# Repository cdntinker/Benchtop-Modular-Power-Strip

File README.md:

Yay...

GitHub borked...

Good thing I'm in the abit of backing things up locally too.

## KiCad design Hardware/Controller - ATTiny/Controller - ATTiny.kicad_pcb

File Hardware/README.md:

# The hardware (duh...)

Each folder here is a standalone KiCAD project for a part of this overall system.

(Tho **KiCAD Customs** is a special case, it contains custom libraries used in this project & **Retired Parts** is aptly named....)

## Backplane
This is the "daisy-chainable" backplane for the modules to plug into.

## Module - *
To create a new module... Just copy one of the **WIP - Prototyping Module** folders, do some renaming & go from there.
* Module - TPS540x
  - a fixed voltage output module based on the TPS540x family of chips.
  - Can be populated with either the 3v3 or 5v0 version (possibly others if they exist)
  - Basic design has dual circuits
  - Options for USB-A/C or XT30 combo footprint
* Module - LM2596S
  - a fixed voltage output module based on the LM2596S
  - Output voltage(s) set via resistors R502/R503 & R602/603
  - Basic design has dual circuits
  - Options for USB-A/C or XT30 combo footprint
* Module - USB QC
  - A QC 2.0 output module
* Module - USB PD Source
  - Take a guess...
  - (I _think_ I've got this one worked out...)

## Master Control Modules
* Controller - ATTiny
  - So far, this is the default.
  - (Seeing as it's basically the same controller as all the modules with USB added...)
* Controller - ESP32
  - WIP
* Controller - ESP8266
  - WIP
* Controller - RP2040
  - WIP

## Testing & Prototyping Modules
* WIP - Prototyping Module
  - Another option as a new module starting point...
* WIP - **Sumpin Random**
  - Could be anything I'm still working through...
* Module - ATTiny Breakout
  - Sort of a module for messing about with the ATTiny...
* Tool - ATTiny Module Flasher
  - A UPDI Module flashing tool
* Tool - ESP Module Flasher
  - An offshoot of the ATTiny Module Flasher

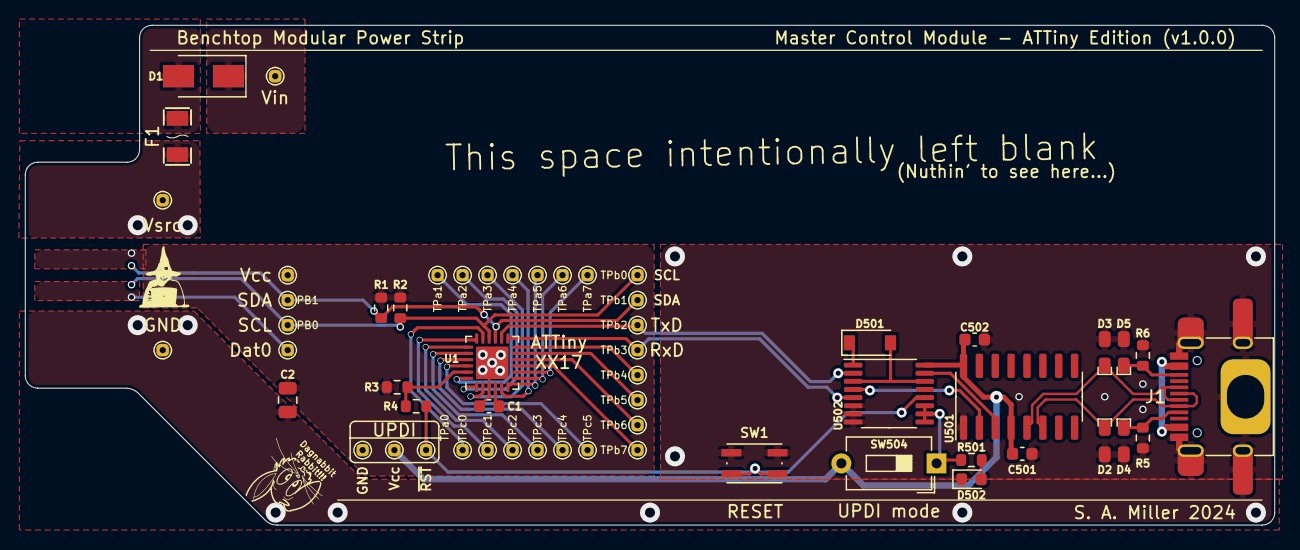
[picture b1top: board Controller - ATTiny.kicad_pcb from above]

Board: 2 copper layers, 100.0 x 40.0 mm, 56 parts (0 on the bottom side), 39 nets.

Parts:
C1: 100nF; C_0603_1608Metric
C2: 4.7uF; C_0805_2012Metric
C501: 10nf; C_0603_1608Metric
C502: 100nf; C_0603_1608Metric
D1: D_Schottky; D_SMA
D2, D3, D4, D5: PGB1010603NR; PGB1010603NRHF
D501: DSK24; D_SOD-123
D502: LED; LED_0603_1608Metric
F1: Polyfuse; F1206
J1: USB_C_Receptacle; USB_C_Receptacle_HRO_TYPE-C-31-M-12
R1, R2, R3: 10k; R_0603_1608Metric
R4: 330R; R_0603_1608Metric
R5, R6: 5k1; R_0603_1608Metric
R501: 2k2; R_0603_1608Metric
SW1: SW_Push; SW_Push_TS273014TP
SW504: SW_DIP_x01; SW_DIP_SPSTx01_Slide_6.7x4.1mm_W7.62mm_P2.54mm_LowProfile
TP1: Vsrc; TestPoint_THTPad_D1.0mm_Drill0.5mm
TP2: Vin; TestPoint_THTPad_D1.0mm_Drill0.5mm
TP3: Dat0; TestPoint_THTPad_D1.0mm_Drill0.5mm
TP4: Dat1; TestPoint_THTPad_D1.0mm_Drill0.5mm
TP5: Dat2; TestPoint_THTPad_D1.0mm_Drill0.5mm
TP6: Dat3; TestPoint_THTPad_D1.0mm_Drill0.5mm
TP7, TP9: GND; TestPoint_THTPad_D1.0mm_Drill0.5mm
TP8: I2C-Vcc; TestPoint_THTPad_D1.0mm_Drill0.5mm
TPa0: ~{RESET}; TestPoint_THTPad_D1.0mm_Drill0.5mm
TPa1, TPa2, TPa3, TPa4, TPa5, TPa6, TPa7: CtrlA; TestPoint_THTPad_D1.0mm_Drill0.5mm
TPb0, TPb1, TPb2, TPb3, TPb4, TPb5, TPb6, TPb7: CtrlB; TestPoint_THTPad_D1.0mm_Drill0.5mm
TPc0, TPc1, TPc2, TPc3, TPc4, TPc5: CtrlC; TestPoint_THTPad_D1.0mm_Drill0.5mm
U1: ATtiny1617; QFN-24-1EP_4x4mm_P0.5mm_EP2.6x2.6mm
U501: CH340C; SOIC-16_3.9x9.9mm_P1.27mm
U502: CD4053B; TSSOP-16_4.4x5mm_P0.65mm

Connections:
/ATTinyXX17/PA0: R3.2, R4.1, U1.23 (~RESET/PA0)
/Source Power Rail/Vprot: D1.2 (A), F1.2
CC1: D4.1, J1.A5 (CC1), R5.1
CC2: D5.1, J1.B5 (CC2), R6.1
GND: C1.2, C2.2, C501.2, C502.2, D2.2, D3.2, D4.2, D5.2, D502.1 (K), J1.A1 (GND), J1.A12 (GND), J1.B1 (GND), J1.B12 (GND), J1.S1 (SHIELD), R5.2, R6.2, SW1.1, TP7.1, TP9.1, U1.3 (GND), U1.25 (GND), U501.1 (GND), U502.6 (INH), U502.7 (VEE), U502.8 (VSS)
I2C-Vcc: C1.1, C2.1, C501.1, C502.1, R1.1, R2.1, R3.1, SW504.2, TP4.1, TP8.1, U1.4 (VCC), U501.4 (V3), U501.16 (VCC), U502.16 (VDD)
unnamed: D501.1 (K), U502.1 (B1)
unnamed: D501.2 (A), U502.3 (C1), U502.14 (A)
unnamed: D502.2 (A), R501.2
unnamed: R501.1, SW504.1, U502.9 (S3), U502.10 (S2), U502.11 (S1)
PA1: TPa1.1, U1.24 (PA1)
PA2: TPa2.1, U1.1 (PA2)
PA3: TPa3.1, U1.2 (PA3)
PA4: TPa4.1, U1.5 (PA4)
PA5: TPa5.1, U1.6 (PA5)
PA6: TPa6.1, U1.7 (PA6)
PA7: TPa7.1, U1.8 (PA7)
PB0: R2.2, TP6.1, TPb0.1, U1.16 (PB0)
PB1: R1.2, TP5.1, TPb1.1, U1.15 (PB1)
PB2: TPb2.1, U1.14 (PB2), U502.2 (B0)
PB3: TPb3.1, U1.13 (PB3), U502.5 (C0)
PB4: TPb4.1, U1.12 (PB4)
PB5: TPb5.1, U1.11 (PB5)
PB6: TPb6.1, U1.10 (PB6)
PB7: TPb7.1, U1.9 (PB7)
PC0: TPc0.1, U1.17 (PC0)
PC1: TPc1.1, U1.18 (PC1)
PC2: TPc2.1, U1.19 (PC2)
PC3: TPc3.1, U1.20 (PC3)
PC4: TPc4.1, U1.21 (PC4)
PC5: TPc5.1, U1.22 (PC5)
RxD: U501.2 (TXD), U502.4 (C)
TxD: U501.3 (RXD), U502.15 (B)
UD+: D3.1, J1.A6 (D+), J1.B6 (D+), U501.5 (UD+)
UD-: D2.1, J1.A7 (D-), J1.B7 (D-), U501.6 (UD-)
Vbus: J1.A4 (VBUS), J1.A9 (VBUS), J1.B4 (VBUS), J1.B9 (VBUS)
Vin: D1.1 (K), TP2.1
Vsrc: F1.1, TP1.1
~RESET: R4.2, SW1.2, TPa0.1, U502.12 (A0)

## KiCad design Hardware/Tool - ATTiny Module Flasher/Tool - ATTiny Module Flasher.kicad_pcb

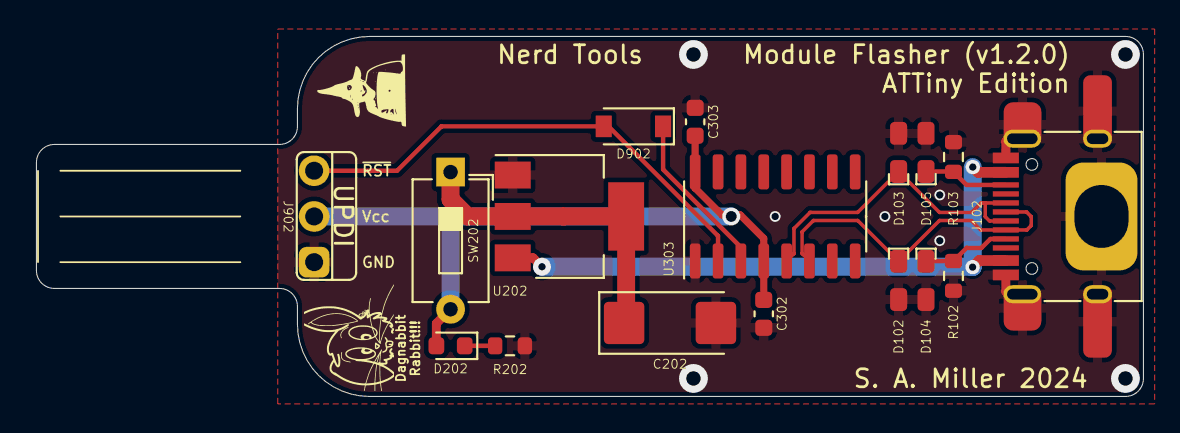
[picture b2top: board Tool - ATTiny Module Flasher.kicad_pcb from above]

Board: 2 copper layers, 61.5 x 20.0 mm, 17 parts (0 on the bottom side), 11 nets.

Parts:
C202: 22uf; CP_EIA-6032-28_Kemet-C_Pad2.25x2.35mm_HandSolder
C302: 10nf; C_0603_1608Metric
C303: 100nf; C_0603_1608Metric
D102, D103, D104, D105: PGB1010603NR; PGB1010603NRHF
D202: LED; LED_0603_1608Metric
D902: DSK24; D_SOD-123
J102: USB_C_Receptacle; USB_C_Receptacle_HRO_TYPE-C-31-M-12
J902: Conn_01x03; UPDI-Pogo
R102, R103: 5k1; R_0603_1608Metric
R202: 2k2; R_0603_1608Metric
SW202: SW_DIP_x01; SW_DIP_SPSTx01_Slide_6.7x4.1mm_W7.62mm_P2.54mm_LowProfile
U202: AMS1117-3.3; SOT-223-3_TabPin2
U303: CH340C; SOIC-16_3.9x9.9mm_P1.27mm

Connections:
CC1: D104.1, J102.A5 (CC1), R102.1
CC2: D105.1, J102.B5 (CC2), R103.1
GND: C202.2, C302.2, C303.2, D102.2, D103.2, D104.2, D105.2, J102.A1 (GND), J102.A12 (GND), J102.B1 (GND), J102.B12 (GND), J102.S1 (SHIELD), J902.1, R102.2, R103.2, R202.2, U202.1 (GND), U303.1 (GND)
I2C-Vcc: C302.1, C303.1, D202.2 (A), J902.2, SW202.2, U303.4 (V3), U303.16 (VCC)
unnamed: C202.1, SW202.1, U202.2 (VO)
unnamed: D202.1 (K), R202.1
RxD: D902.2 (A), J902.3, U303.2 (TXD)
TxD: D902.1 (K), U303.3 (RXD)
UD+: D103.1, J102.A6 (D+), J102.B6 (D+), U303.5 (UD+)
UD-: D102.1, J102.A7 (D-), J102.B7 (D-), U303.6 (UD-)
Vbus: J102.A4 (VBUS), J102.A9 (VBUS), J102.B4 (VBUS), J102.B9 (VBUS), U202.3 (VI)

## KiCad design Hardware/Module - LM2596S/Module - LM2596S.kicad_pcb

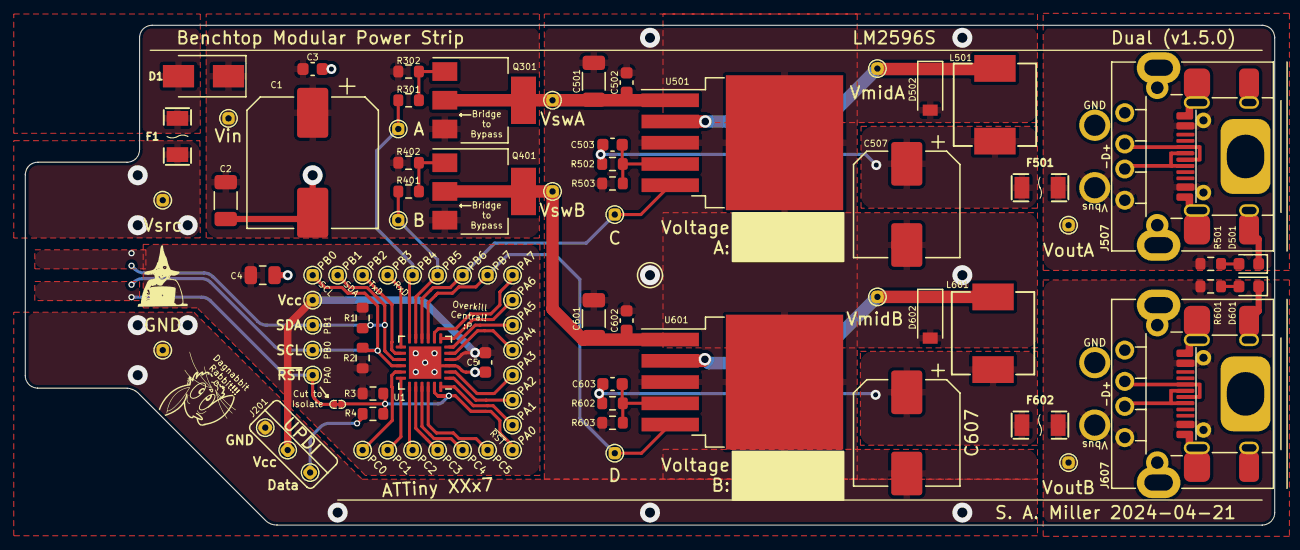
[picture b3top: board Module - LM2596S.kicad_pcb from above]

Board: 2 copper layers, 100.0 x 40.0 mm, 85 parts (0 on the bottom side), 43 nets.

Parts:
C1: 220uF; CP_Elec_10x10
C2, C501, C601: 10uF; C_1206_3216Metric
C3, C5, C502, C602: 100nF; C_0603_1608Metric
C4: 4.7uF; C_0805_2012Metric
C503, C603: 200p; C_0603_1608Metric
C507, C607: 220uF; CP_Elec_8x10
D1: D_Schottky; D_SMA
D501, D601: LED; LED_0603_1608Metric
D502, D602: PMEG6010CEH; D_SOD-123
F1, F501, F602: Polyfuse; F1206
J201: UPDI Connection; UPDI_connection
J507, J607: USB_A+C+XT30
JP201: Jumper_2_Bridged; tinySJ-Bridged
L501, L601: 68uH; IND-SMD_L7.1-W6.6
PA0, PA1, PA2, PA3, PA4, PA5, PA6, PA7: CtrlA; TestPoint_THTPad_D1.0mm_Drill0.5mm
PB0, PB1, PB2, PB3, PB4, PB5, PB6, PB7: CtrlB; TestPoint_THTPad_D1.0mm_Drill0.5mm
PC0, PC1, PC2, PC3, PC4, PC5: CtrlC; TestPoint_THTPad_D1.0mm_Drill0.5mm
Q301, Q401: ZXMP4A16G; SOT-223-3_TabPin2
R1, R2, R3, R302, R402: 10k; R_0603_1608Metric
R4: 330R; R_0603_1608Metric
R301, R401: 100R; R_0603_1608Metric
R501, R601: ?; R_0603_1608Metric
R502, R602: 3K; R_0603_1608Metric
R503, R603: 1K; R_0603_1608Metric
TP1: Vsrc; TestPoint_THTPad_D1.0mm_Drill0.5mm
TP2: Vin; TestPoint_THTPad_D1.0mm_Drill0.5mm
TP3: Dat0; TestPoint_THTPad_D1.0mm_Drill0.5mm
TP4: Dat1; TestPoint_THTPad_D1.0mm_Drill0.5mm
TP5: Dat2; TestPoint_THTPad_D1.0mm_Drill0.5mm
TP6: Dat3; TestPoint_THTPad_D1.0mm_Drill0.5mm
TP7: GND; TestPoint_THTPad_D1.0mm_Drill0.5mm
TP301, TP401: CtrlA; TestPoint_THTPad_D1.0mm_Drill0.5mm
TP302: VswA; TestPoint_THTPad_D1.0mm_Drill0.5mm
TP402: VswB; TestPoint_THTPad_D1.0mm_Drill0.5mm
TP501, TP601: Vout1; TestPoint_THTPad_D1.0mm_Drill0.5mm
TP502, TP503, TP602, TP603: Vmid; TestPoint_THTPad_D1.0mm_Drill0.5mm
U1: ATtiny1617; QFN-24-1EP_4x4mm_P0.5mm_EP2.6x2.6mm
U501, U601: LM2596S-ADJ; TO-263-5_TabPin3

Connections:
/OUT-A/Feedback A: C503.2, R502.2, R503.1, U501.4 (FB)
/OUT-A/Vmid A: D502.1 (K), L501.1, TP503.1, U501.2 (OUT)
/OUT-B/Feedback B: C603.2, R602.2, R603.1, U601.4 (FB)
/OUT-B/Vmid B: D602.1 (K), L601.1, TP603.1, U601.2 (OUT)
/Source Power Rail/Vprot: D1.2 (A), F1.2
Dat0: JP201.1 (A), TP3.1
GND: C1.2, C2.2, C3.2, C4.2, C5.2, C501.2, C502.2, C507.2, C601.2, C602.2, C607.2, D501.1 (K), D502.2 (A), D601.1 (K), D602.2 (A), J201.1, J507.4 (GND), J507.5 (Shield), J607.4 (GND), J607.5 (Shield), R503.2, R603.2, TP7.1, U1.3 (GND), U1.25 (GND), U501.3 (GND), U601.3 (GND)
I2C-Vcc: C4.1, C5.1, J201.2, R1.1, R2.1, R3.1, TP4.1, U1.4 (VCC)
unnamed: C503.1, C507.1, F501.1, L501.2, R502.1
unnamed: C603.1, C607.1, F602.1, L601.2, R602.1
unnamed: D501.2 (A), R501.2
unnamed: D601.2 (A), R601.2
unnamed: Q301.1 (G), R301.2, R302.2
unnamed: Q401.1 (G), R401.2, R402.2
PA0: JP201.2 (B), PA0.1, R3.2, R4.1, U1.23 (~RESET/PA0)
PA1: PA1.1, U1.24 (PA1)
PA2: PA2.1, U1.1 (PA2)
PA3: PA3.1, U1.2 (PA3)
PA4: PA4.1, U1.5 (PA4)
PA5: PA5.1, U1.6 (PA5)
PA6: PA6.1, U1.7 (PA6)
PA7: PA7.1, U1.8 (PA7)
PB0: PB0.1, R2.2, TP6.1, U1.16 (PB0)
PB1: PB1.1, R1.2, TP5.1, U1.15 (PB1)
PB2: PB2.1, U1.14 (PB2)
PB3: PB3.1, U1.13 (PB3)
PB4: PB4.1, R301.1, TP301.1, U1.12 (PB4)
PB5: PB5.1, R401.1, TP401.1, U1.11 (PB5)
PB6: PB6.1, TP502.1, U1.10 (PB6), U501.5 (~ON/OFF)
PB7: PB7.1, TP602.1, U1.9 (PB7), U601.5 (~ON/OFF)
PC0: PC0.1, U1.17 (PC0)
PC1: PC1.1, U1.18 (PC1)
PC2: PC2.1, U1.19 (PC2)
PC3: PC3.1, U1.20 (PC3)
PC4: PC4.1, U1.21 (PC4)
PC5: PC5.1, U1.22 (PC5)
Vin: C1.1, C2.1, C3.1, D1.1 (K), Q301.3 (S), Q401.3 (S), R302.1, R402.1, TP2.1
VoutA: F501.2, J507.1 (VBUS), R501.1, TP501.1
VoutB: F602.2, J607.1 (VBUS), R601.1, TP601.1
Vsrc: F1.1, TP1.1
VswA: C501.1, C502.1, Q301.2 (D), TP302.1, U501.1 (VIN)
VswB: C601.1, C602.1, Q401.2 (D), TP402.1, U601.1 (VIN)
~RESET: J201.3, R4.2

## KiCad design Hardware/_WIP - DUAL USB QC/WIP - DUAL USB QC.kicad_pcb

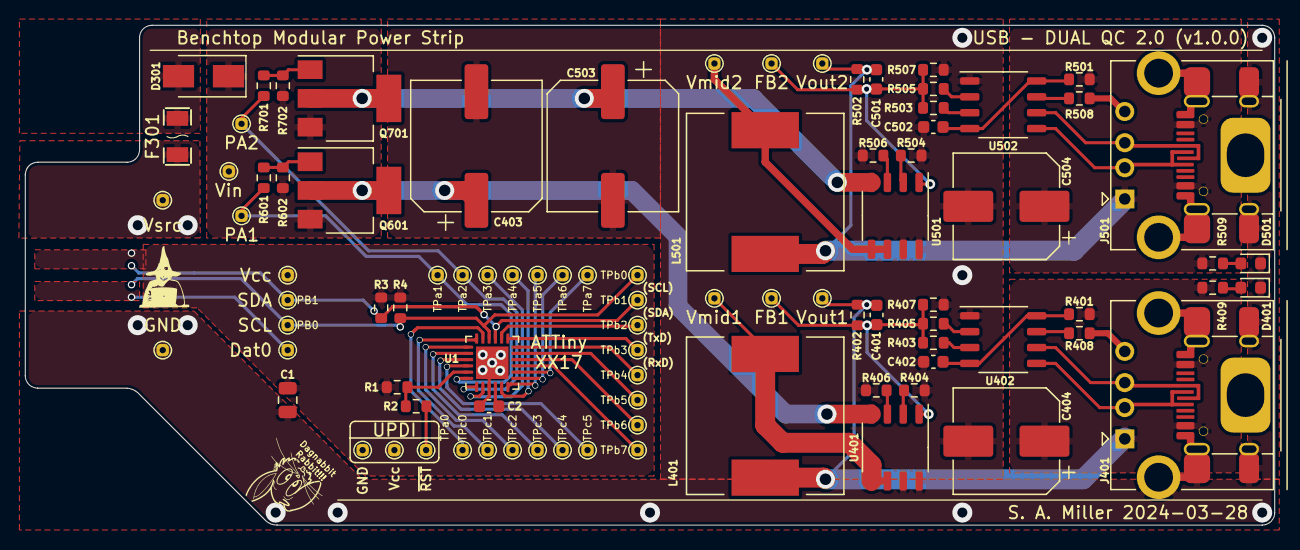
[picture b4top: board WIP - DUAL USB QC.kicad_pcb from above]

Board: 2 copper layers, 100.0 x 40.0 mm, 90 parts (0 on the bottom side), 56 nets.

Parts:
C1: 4.7uF; C_0805_2012Metric
C2: 100nF; C_0603_1608Metric
C401, C501: 200p; C_0603_1608Metric
C402, C502: 220n; C_0603_1608Metric
C403, C503: 100u; CP_Elec_10x7.7
C404, C504: 220u; CP_Elec_8x6.5
D301: D_Schottky; D_SMA
D401, D501: LED; LED_0603_1608Metric
F301: Polyfuse; F1206
J401, J501: USB_A; USB_A+C
L401, L501: 47uH; L_12x12mm_H8mm
Q601, Q701: ZXMP4A16G; SOT-223-3_TabPin2
R1, R3, R4, R602, R702: 10k; R_0603_1608Metric
R2: 330R; R_0603_1608Metric
R401, R501: 2K2; R_0603_1608Metric
R402, R502: 470K; R_0603_1608Metric
R403, R503: 187K; R_0603_1608Metric
R404, R504: NC; R_0603_1608Metric
R405, R505: 137K; R_0603_1608Metric
R406, R506: 82K; R_0603_1608Metric
R407, R507: 150K; R_0603_1608Metric
R408, R508: 127K; R_0603_1608Metric
R409, R509: ?; R_0603_1608Metric
R601, R701: 100; R_0603_1608Metric
TP1: I2C-Vcc; TestPoint_THTPad_D1.0mm_Drill0.5mm
TP4, TP303: GND; TestPoint_THTPad_D1.0mm_Drill0.5mm
TP5: Dat0; TestPoint_THTPad_D1.0mm_Drill0.5mm
TP6: Dat1; TestPoint_THTPad_D1.0mm_Drill0.5mm
TP7: Dat2; TestPoint_THTPad_D1.0mm_Drill0.5mm
TP8: Dat3; TestPoint_THTPad_D1.0mm_Drill0.5mm
TP301: Vsrc; TestPoint_THTPad_D1.0mm_Drill0.5mm
TP302: Vin; TestPoint_THTPad_D1.0mm_Drill0.5mm
TP401: Vmid1; TestPoint_THTPad_D1.0mm_Drill0.5mm
TP402: Vout1; TestPoint_THTPad_D1.0mm_Drill0.5mm
TP403: FB1; TestPoint_THTPad_D1.0mm_Drill0.5mm
TP501: Vmid2; TestPoint_THTPad_D1.0mm_Drill0.5mm
TP502: Vout2; TestPoint_THTPad_D1.0mm_Drill0.5mm
TP503: FB2; TestPoint_THTPad_D1.0mm_Drill0.5mm
TPa0: ~{RESET}; TestPoint_THTPad_D1.0mm_Drill0.5mm
TPa1, TPa2, TPa3, TPa4, TPa5, TPa6, TPa7, TPa601, TPa701: CtrlA; TestPoint_THTPad_D1.0mm_Drill0.5mm
TPb0, TPb1, TPb2, TPb3, TPb4, TPb5, TPb6, TPb7: CtrlB; TestPoint_THTPad_D1.0mm_Drill0.5mm
TPc0, TPc1, TPc2, TPc3, TPc4, TPc5: CtrlC; TestPoint_THTPad_D1.0mm_Drill0.5mm
U1: ATtiny1617; QFN-24-1EP_4x4mm_P0.5mm_EP2.6x2.6mm
U401, U501: PL2733A; SSOP-8_3.9x5.05mm_P1.27mm
U402, U502: FP6600; SSOP-8_3.9x5.05mm_P1.27mm

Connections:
/ATTinyXX17/PA0: R1.2, R2.1, U1.23 (~RESET/PA0)
/Source Power Rail/Vprot: D301.2 (A), F301.2
/USB-QC1/Vmid2: L501.1, TP501.1, U501.5 (SW), U501.6 (SW)
/USB-QC/Vmid1: L401.1, TP401.1, U401.5 (SW), U401.6 (SW)
GND: C1.2, C2.2, C402.1, C403.2, C404.2, C502.1, C503.2, C504.2, D401.1 (K), D501.1 (K), J401.4 (GND), J401.5 (Shield), J501.4 (GND), J501.5 (Shield), R404.2, R406.2, R407.2, R408.2, R504.2, R506.2, R507.2, R508.2, TP4.1, TP303.1, U1.3 (GND), U1.25 (GND), U401.7 (GND), U401.8 (GND), U402.1 (GND), U501.7 (GND), U501.8 (GND), U502.1 (GND)
I2C-Vcc: C1.1, C2.1, R1.1, R3.1, R4.1, TP1.1, TP6.1, U1.4 (VCC)
unnamed: C401.2, R402.2, R403.2, R405.2, R407.1, TP403.1, U401.1 (FB)
unnamed: C402.2, R401.2, U402.4 (V3), U402.8 (BP)
unnamed: C501.2, R502.2, R503.2, R505.2, R507.1, TP503.1, U501.1 (FB)
unnamed: C502.2, R501.2, U502.4 (V3), U502.8 (BP)
unnamed: D401.2 (A), R409.2
unnamed: D501.2 (A), R509.2
unnamed: J401.2 (D-), U402.5 (D1)
unnamed: J401.3 (D+), U402.6 (D+)
unnamed: J501.2 (D-), U502.5 (D1)
unnamed: J501.3 (D+), U502.6 (D+)
unnamed: Q601.1 (G), R601.2, R602.2
unnamed: Q701.1 (G), R701.2, R702.2
unnamed: R403.1, U402.3 (V2)
unnamed: R404.1, U401.2 (RT)
unnamed: R405.1, U402.2 (V1)
unnamed: R406.1, U401.3 (ILMI)
unnamed: R408.1, U402.7 (R)
unnamed: R503.1, U502.3 (V2)
unnamed: R504.1, U501.2 (RT)
unnamed: R505.1, U502.2 (V1)
unnamed: R506.1, U501.3 (ILMI)
unnamed: R508.1, U502.7 (R)
PA1: R601.1, TPa1.1, TPa601.1, U1.24 (PA1)
PA2: R701.1, TPa2.1, TPa701.1, U1.1 (PA2)
PA3: TPa3.1, U1.2 (PA3)
PA4: TPa4.1, U1.5 (PA4)
PA5: TPa5.1, U1.6 (PA5)
PA6: TPa6.1, U1.7 (PA6)
PA7: TPa7.1, U1.8 (PA7)
PB0: R4.2, TP8.1, TPb0.1, U1.16 (PB0)
PB1: R3.2, TP7.1, TPb1.1, U1.15 (PB1)
PB2: TPb2.1, U1.14 (PB2)
PB3: TPb3.1, U1.13 (PB3)
PB4: TPb4.1, U1.12 (PB4)
PB5: TPb5.1, U1.11 (PB5)
PB6: TPb6.1, U1.10 (PB6)
PB7: TPb7.1, U1.9 (PB7)
PC0: TPc0.1, U1.17 (PC0)
PC1: TPc1.1, U1.18 (PC1)
PC2: TPc2.1, U1.19 (PC2)
PC3: TPc3.1, U1.20 (PC3)
PC4: TPc4.1, U1.21 (PC4)
PC5: TPc5.1, U1.22 (PC5)
Vin: D301.1 (K), Q601.3 (S), Q701.3 (S), R602.1, R702.1, TP302.1
Vout1: C401.1, C404.1, J401.1 (VBUS), L401.2, R401.1, R402.1, R409.1, TP402.1
Vout2: C501.1, C504.1, J501.1 (VBUS), L501.2, R501.1, R502.1, R509.1, TP502.1
Vsrc: F301.1, TP301.1
VswA: C403.1, Q601.2 (D), U401.4 (VIN)
VswB: C503.1, Q701.2 (D), U501.4 (VIN)
~RESET: R2.2, TPa0.1

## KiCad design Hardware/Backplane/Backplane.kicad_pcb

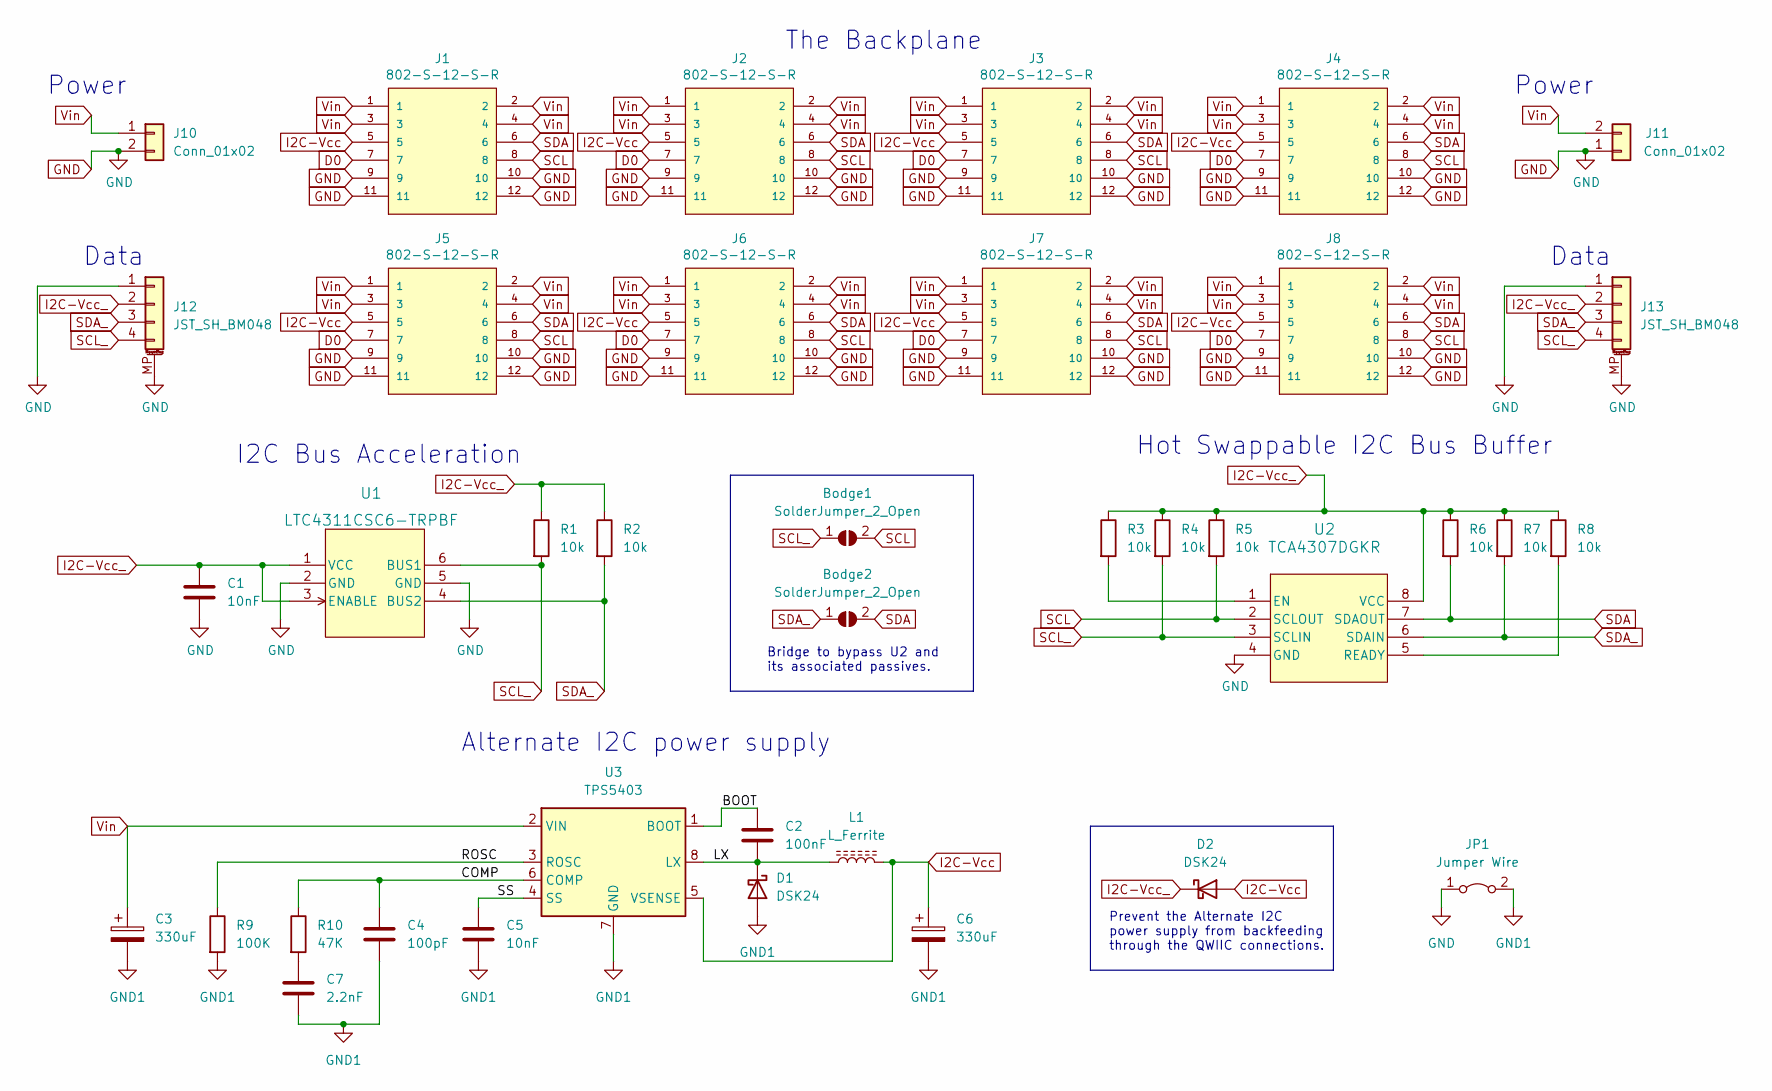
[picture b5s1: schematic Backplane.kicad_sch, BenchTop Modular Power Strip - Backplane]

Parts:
Bodge1, Bodge2: SolderJumper_2_Open; SolderJumper-2_P1.3mm_Open_RoundedPad1.0x1.5mm
C1, C5: 10nF; C_0603_1608Metric; LCSC C107059
C2: 100nF; C_0603_1608Metric; LCSC C14663
C3, C6: 330uF; CP_Elec_8x10; LCSC C178599
C4: 100pF; C_0603_1608Metric; LCSC C44567
C7: 2.2nF; C_0603_1608Metric; LCSC C107082
D1, D2: DSK24; D_SOD-123; LCSC C908229
J1, J2, J3, J4, J5, J6, J7, J8: 802-S-12-S-R; CONN-TH_12P-P2.54_WINGTAT_ED12BGFBK; PARTREV April 28, 2021; LCSC C5173290
J10, J11: Conn_01x02; CONN-TH_KF58RM-10.0-2P; LCSC C707718
J12, J13: JST_SH_BM048; JST_SH_BM04B-SRSS-TB_1x04-1MP_P1.00mm_Vertical; LCSC C145961
JP1: Jumper Wire; Jumper-Wire_25mm_Blue
L1: L_Ferrite; IND-SMD_L7.1-W6.6; LCSC C2983095
R1, R2, R3, R4, R5, R6, R7, R8: 10k; R_0603_1608Metric; LCSC C25804
R9: 100K; R_0603_1608Metric; LCSC C25803
R10: 47K; R_0603_1608Metric; LCSC C25819
U1: LTC4311CSC6-TRPBF; SOT-6_SC_LIT; LCSC C580856
U2: TCA4307DGKR; SOIC8_DGK_TEX; LCSC C880333
U3: TPS5403; SOIC-8_3.9x4.9mm_P1.27mm; LCSC C962080

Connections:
/BOOT: C2.1, U3.1 (BOOT)
/COMP: C4.1, R10.1, U3.6 (COMP)
/LX: C2.2, D1.1 (K), L1.1, U3.8 (LX)
/ROSC: R9.1, U3.3 (ROSC)
/SS: C5.1, U3.4 (SS)
D0: J1.7, J2.7, J3.7, J4.7, J5.7, J6.7, J7.7, J8.7
GND: C1.2, J1.9, J1.10, J1.11, J1.12, J2.9, J2.10, J2.11, J2.12, J3.9, J3.10, J3.11, J3.12, J4.9, J4.10, J4.11, J4.12, J5.9, J5.10, J5.11, J5.12, J6.9, J6.10, J6.11, J6.12, J7.9, J7.10, J7.11, J7.12, J8.9, J8.10, J8.11, J8.12, J10.2, J11.1, J12.1, J12.MP (MountPin), J13.1, J13.MP (MountPin), JP1.1 (A), U1.2 (GND), U1.5 (GND), U2.4 (GND)
GND1: C3.2, C4.2, C5.2, C6.2, C7.2, D1.2 (A), JP1.2 (B), R9.2, U3.7 (GND)
I2C-Vcc: C6.1, D2.2 (A), J1.5, J2.5, J3.5, J4.5, J5.5, J6.5, J7.5, J8.5, L1.2, U3.5 (VSENSE)
I2C-Vcc_: C1.1, D2.1 (K), J12.2, J13.2, R1.1, R2.1, R3.1, R4.1, R5.1, R6.1, R7.1, R8.1, U1.1 (VCC), U1.3 (ENABLE), U2.8 (VCC)
unnamed: C7.1, R10.2
unnamed: R3.2, U2.1 (EN)
unnamed: R8.2, U2.5 (READY)
SCL: Bodge1.2 (B), J1.8, J2.8, J3.8, J4.8, J5.8, J6.8, J7.8, J8.8, R5.2, U2.2 (SCLOUT)
SCL_: Bodge1.1 (A), J12.4, J13.4, R1.2, R4.2, U1.6 (BUS1), U2.3 (SCLIN)
SDA: Bodge2.2 (B), J1.6, J2.6, J3.6, J4.6, J5.6, J6.6, J7.6, J8.6, R6.2, U2.7 (SDAOUT)
SDA_: Bodge2.1 (A), J12.3, J13.3, R2.2, R7.2, U1.4 (BUS2), U2.6 (SDAIN)
Vin: C3.1, J1.1, J1.2, J1.3, J1.4, J2.1, J2.2, J2.3, J2.4, J3.1, J3.2, J3.3, J3.4, J4.1, J4.2, J4.3, J4.4, J5.1, J5.2, J5.3, J5.4, J6.1, J6.2, J6.3, J6.4, J7.1, J7.2, J7.3, J7.4, J8.1, J8.2, J8.3, J8.4, J10.1, J11.2, U3.2 (VIN)

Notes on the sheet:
Alternate I2C power supply
Prevent the Alternate I2C power supply from backfeeding through the QWIIC connections.
Data
Bridge to bypass U2 and its associated passives.
I2C Bus Acceleration
Hot Swappable I2C Bus Buffer
Power
The Backplane

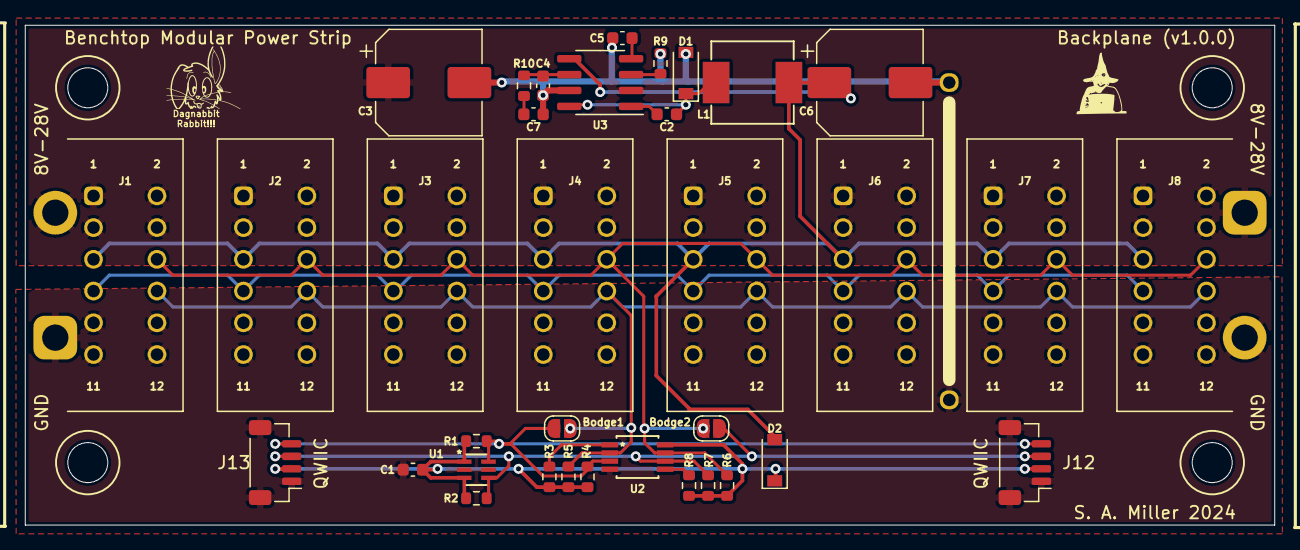
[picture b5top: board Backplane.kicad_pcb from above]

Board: 2 copper layers, 100.0 x 40.0 mm, 38 parts (0 on the bottom side), 18 nets.

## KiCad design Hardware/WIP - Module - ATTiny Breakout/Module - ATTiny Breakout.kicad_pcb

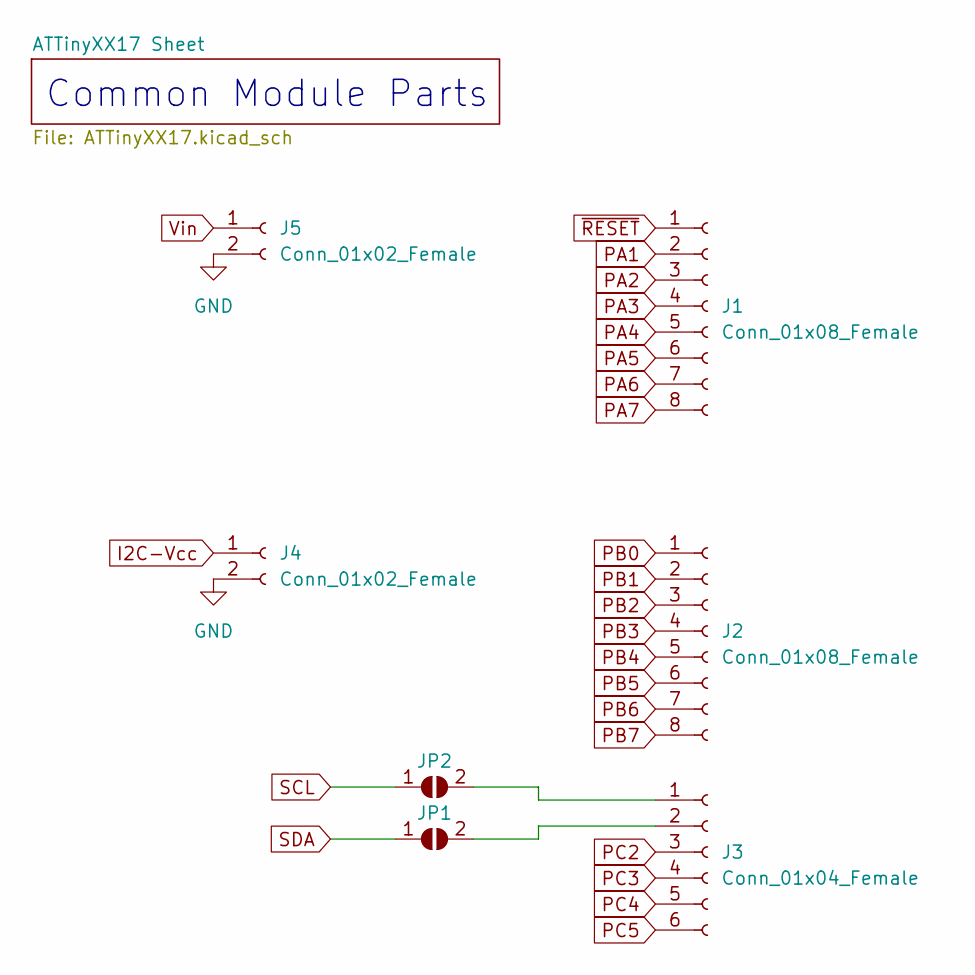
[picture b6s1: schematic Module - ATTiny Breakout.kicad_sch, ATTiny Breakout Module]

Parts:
J1, J2: Conn_01x08_Female; PinSocket_1x08_P2.54mm_Vertical
J3: Conn_01x04_Female; PinSocket_1x06_P2.54mm_Vertical
J4, J5: Conn_01x02_Female; PinSocket_1x02_P2.54mm_Vertical
JP1, JP2: SolderJumper_2_Open; SolderJumper-2_P1.3mm_Open_RoundedPad1.0x1.5mm

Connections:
GND: J4.2, J5.2; also elsewhere on the board
I2C-Vcc: J4.1; also elsewhere on the board
unnamed: J3.1, JP2.2 (B)
unnamed: J3.2, JP1.2 (B)
PA1: J1.2; also elsewhere on the board
PA2: J1.3; also elsewhere on the board
PA3: J1.4; also elsewhere on the board
PA4: J1.5; also elsewhere on the board
PA5: J1.6; also elsewhere on the board
PA6: J1.7; also elsewhere on the board
PA7: J1.8; also elsewhere on the board
PB0: J2.1; also elsewhere on the board
PB1: J2.2; also elsewhere on the board
PB2: J2.3; also elsewhere on the board
PB3: J2.4; also elsewhere on the board
PB4: J2.5; also elsewhere on the board
PB5: J2.6; also elsewhere on the board
PB6: J2.7; also elsewhere on the board
PB7: J2.8; also elsewhere on the board
PC2: J3.3; also elsewhere on the board
PC3: J3.4; also elsewhere on the board
PC4: J3.5; also elsewhere on the board
PC5: J3.6; also elsewhere on the board
SCL: JP2.1 (A); also elsewhere on the board
SDA: JP1.1 (A); also elsewhere on the board
Vin: J5.1; also elsewhere on the board
~RESET: J1.1; also elsewhere on the board

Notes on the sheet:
Common Module Parts

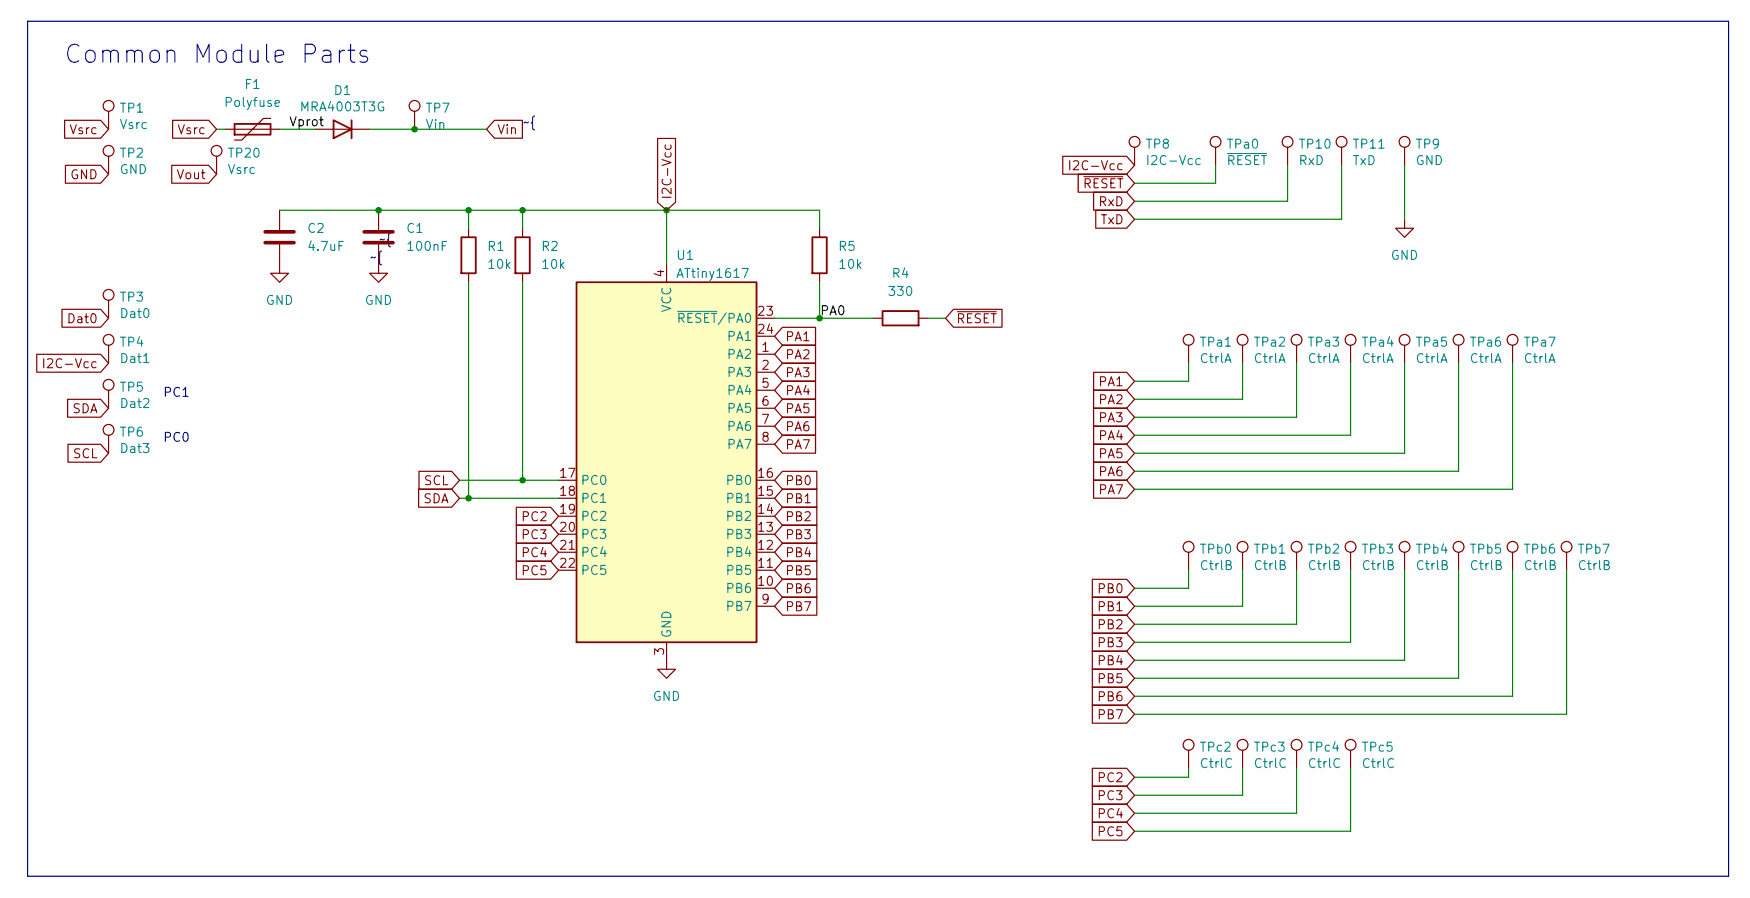
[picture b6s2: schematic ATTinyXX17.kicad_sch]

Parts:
C1: 100nF; C_0603_1608Metric
C2: 4.7uF; C_0805_2012Metric
D1: MRA4003T3G; D_SMA
F1: Polyfuse; F1206; LCSC C2977524 (random choice)
R1, R2, R5: 10k; R_0603_1608Metric
R4: 330; R_0603_1608Metric
TP1, TP20: Vsrc; TestPoint_THTPad_D1.0mm_Drill0.5mm
TP2, TP9: GND; TestPoint_THTPad_D1.0mm_Drill0.5mm
TP3: Dat0; TestPoint_THTPad_D1.0mm_Drill0.5mm
TP4: Dat1; TestPoint_THTPad_D1.0mm_Drill0.5mm
TP5: Dat2; TestPoint_THTPad_D1.0mm_Drill0.5mm
TP6: Dat3; TestPoint_THTPad_D1.0mm_Drill0.5mm
TP7: Vin; TestPoint_THTPad_D1.0mm_Drill0.5mm
TP8: I2C-Vcc; TestPoint_THTPad_D1.0mm_Drill0.5mm
TP10: RxD; TestPoint_THTPad_D1.0mm_Drill0.5mm
TP11: TxD; TestPoint_THTPad_D1.0mm_Drill0.5mm
TPa0: ~{RESET}; TestPoint_THTPad_D1.0mm_Drill0.5mm
TPa1, TPa2, TPa3, TPa4, TPa5, TPa6, TPa7: CtrlA; TestPoint_THTPad_D1.0mm_Drill0.5mm
TPb0, TPb1, TPb2, TPb3, TPb4, TPb5, TPb6, TPb7: CtrlB; TestPoint_THTPad_D1.0mm_Drill0.5mm
TPc2, TPc3, TPc4, TPc5: CtrlC; TestPoint_THTPad_D1.0mm_Drill0.5mm
U1: ATtiny1617; QFN-24-1EP_4x4mm_P0.5mm_EP2.6x2.6mm

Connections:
/ATTinyXX17 Sheet/PA0: R4.1, R5.2, U1.23 (~RESET/PA0)
/ATTinyXX17 Sheet/Vprot: D1.2 (A), F1.2
Dat0: TP3.1
GND: C1.2, C2.2, TP2.1, TP9.1, U1.3 (GND), U1.25 (GND); also elsewhere on the board
I2C-Vcc: C1.1, C2.1, R1.1, R2.1, R5.1, TP4.1, TP8.1, U1.4 (VCC); also elsewhere on the board
PA1: TPa1.1, U1.24 (PA1); also elsewhere on the board
PA2: TPa2.1, U1.1 (PA2); also elsewhere on the board
PA3: TPa3.1, U1.2 (PA3); also elsewhere on the board
PA4: TPa4.1, U1.5 (PA4); also elsewhere on the board
PA5: TPa5.1, U1.6 (PA5); also elsewhere on the board
PA6: TPa6.1, U1.7 (PA6); also elsewhere on the board
PA7: TPa7.1, U1.8 (PA7); also elsewhere on the board
PB0: TPb0.1, U1.16 (PB0); also elsewhere on the board
PB1: TPb1.1, U1.15 (PB1); also elsewhere on the board
PB2: TPb2.1, U1.14 (PB2); also elsewhere on the board
PB3: TPb3.1, U1.13 (PB3); also elsewhere on the board
PB4: TPb4.1, U1.12 (PB4); also elsewhere on the board
PB5: TPb5.1, U1.11 (PB5); also elsewhere on the board
PB6: TPb6.1, U1.10 (PB6); also elsewhere on the board
PB7: TPb7.1, U1.9 (PB7); also elsewhere on the board
PC2: TPc2.1, U1.19 (PC2); also elsewhere on the board
PC3: TPc3.1, U1.20 (PC3); also elsewhere on the board
PC4: TPc4.1, U1.21 (PC4); also elsewhere on the board
PC5: TPc5.1, U1.22 (PC5); also elsewhere on the board
SCL: R2.2, TP6.1, U1.17 (PC0); also elsewhere on the board
SDA: R1.2, TP5.1, U1.18 (PC1); also elsewhere on the board
Vin: D1.1 (K), TP7.1; also elsewhere on the board
Vsrc: F1.1, TP1.1
~RESET: R4.2, TPa0.1; also elsewhere on the board

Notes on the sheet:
PC0
Common Module Parts
PC1

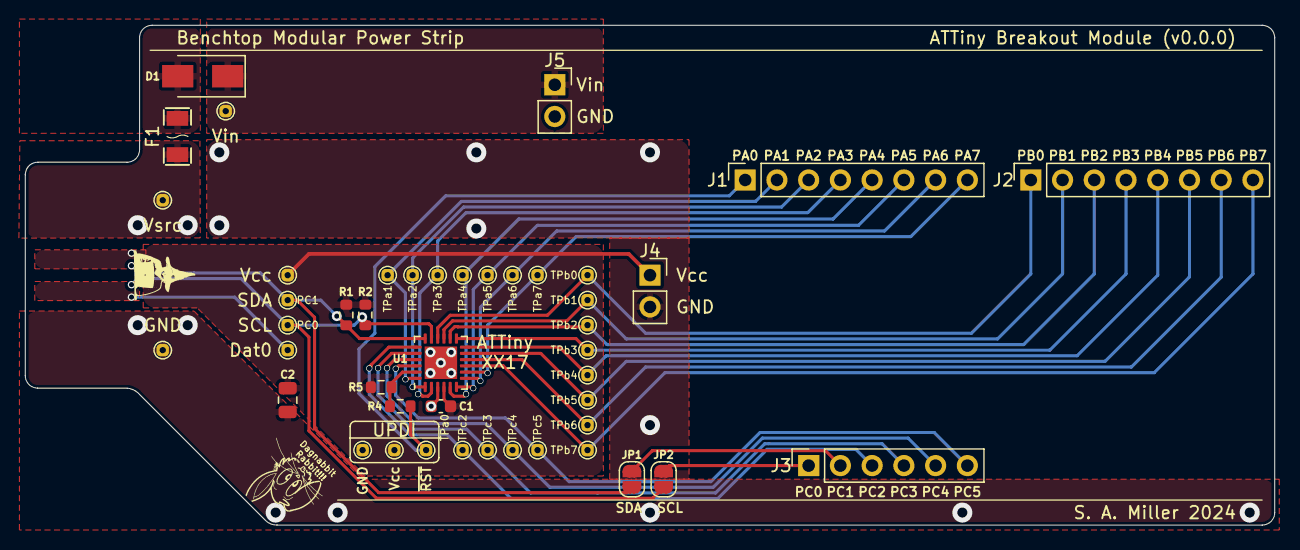
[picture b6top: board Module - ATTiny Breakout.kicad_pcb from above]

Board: 2 copper layers, 100.0 x 40.0 mm, 45 parts (0 on the bottom side), 30 nets.

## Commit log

2024-05-13 updating tools designs
2025-01-10 Added a reset button to ATTiny controller board
